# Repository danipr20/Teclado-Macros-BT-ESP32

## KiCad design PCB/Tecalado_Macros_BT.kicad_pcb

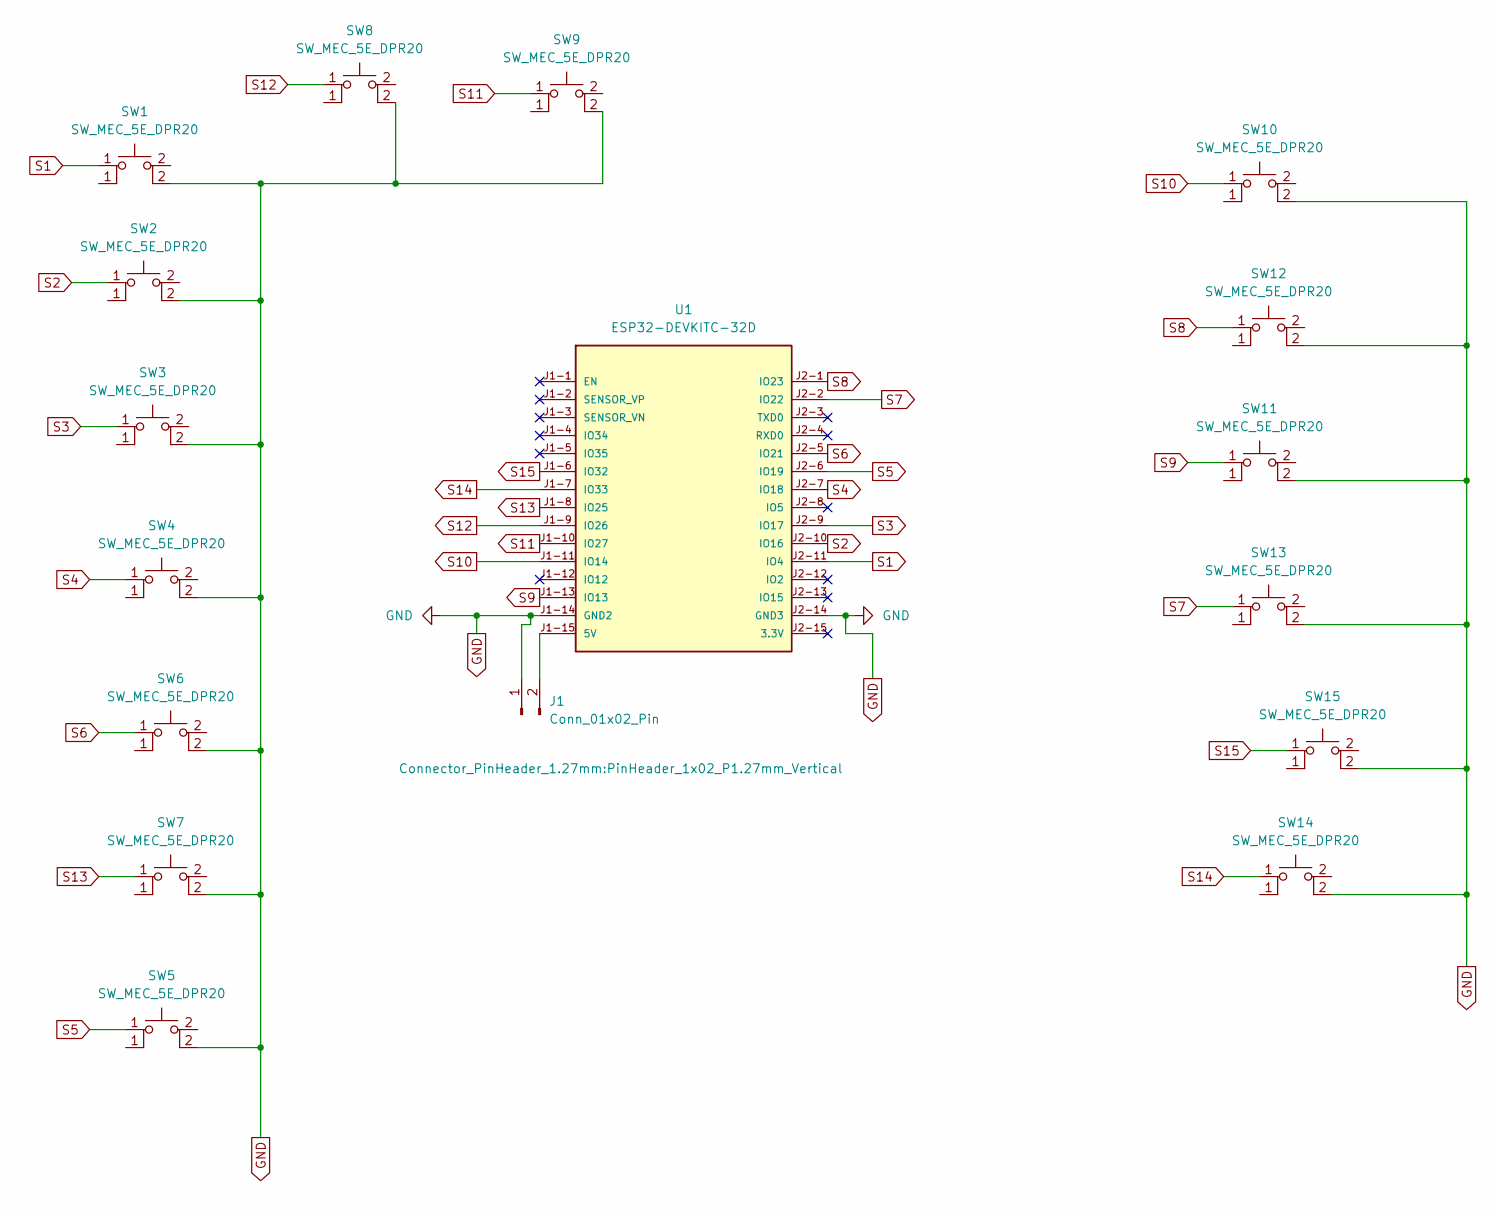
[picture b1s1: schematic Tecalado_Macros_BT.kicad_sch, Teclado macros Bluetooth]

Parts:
J1: Conn_01x02_Pin; PinHeader_1x02_P1.27mm_Vertical
SW1, SW2, SW3, SW4, SW5, SW6, SW7, SW8, SW9, SW10, SW11, SW12, SW13, SW14, SW15: SW_MEC_5E_DPR20; SW_PUSH_6mm_H7.3mm
U1: ESP32-DEVKITC-32D; MODULE_ESP32-DEVKITC-32D; PARTREV V4

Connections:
GND: J1.1, SW1.2, SW2.2, SW3.2, SW4.2, SW5.2, SW6.2, SW7.2, SW8.2, SW9.2, SW10.2, SW11.2, SW12.2, SW13.2, SW14.2, SW15.2, U1.J1-14 (GND2), U1.J2-14 (GND3)
unnamed: J1.2, U1.J1-15 (5V)
S1: SW1.1, U1.J2-11 (IO4)
S2: SW2.1, U1.J2-10 (IO16)
S3: SW3.1, U1.J2-9 (IO17)
S4: SW4.1, U1.J2-7 (IO18)
S5: SW5.1, U1.J2-6 (IO19)
S6: SW6.1, U1.J2-5 (IO21)
S7: SW13.1, U1.J2-2 (IO22)
S8: SW12.1, U1.J2-1 (IO23)
S9: SW11.1, U1.J1-13 (IO13)
S10: SW10.1, U1.J1-11 (IO14)
S11: SW9.1, U1.J1-10 (IO27)
S12: SW8.1, U1.J1-9 (IO26)
S13: SW7.1, U1.J1-8 (IO25)
S14: SW14.1, U1.J1-7 (IO33)
S15: SW15.1, U1.J1-6 (IO32)

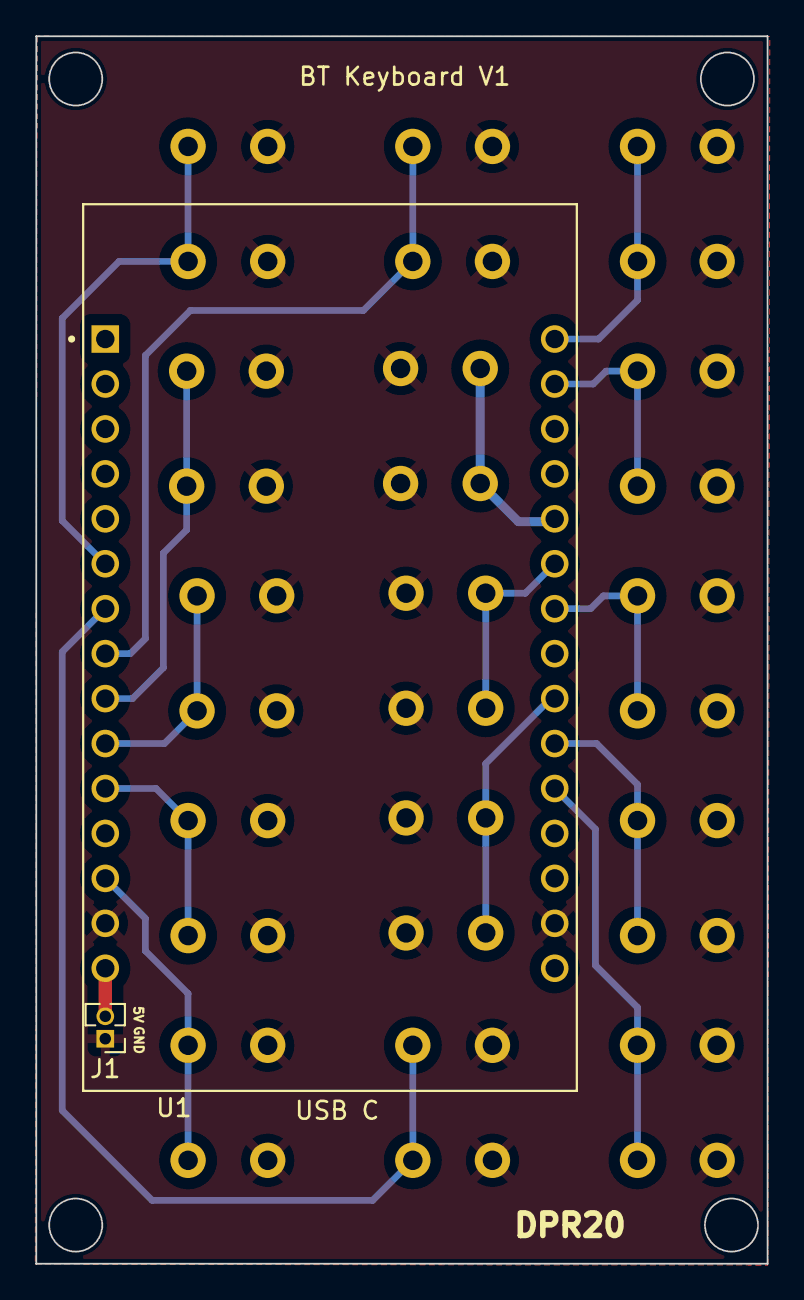
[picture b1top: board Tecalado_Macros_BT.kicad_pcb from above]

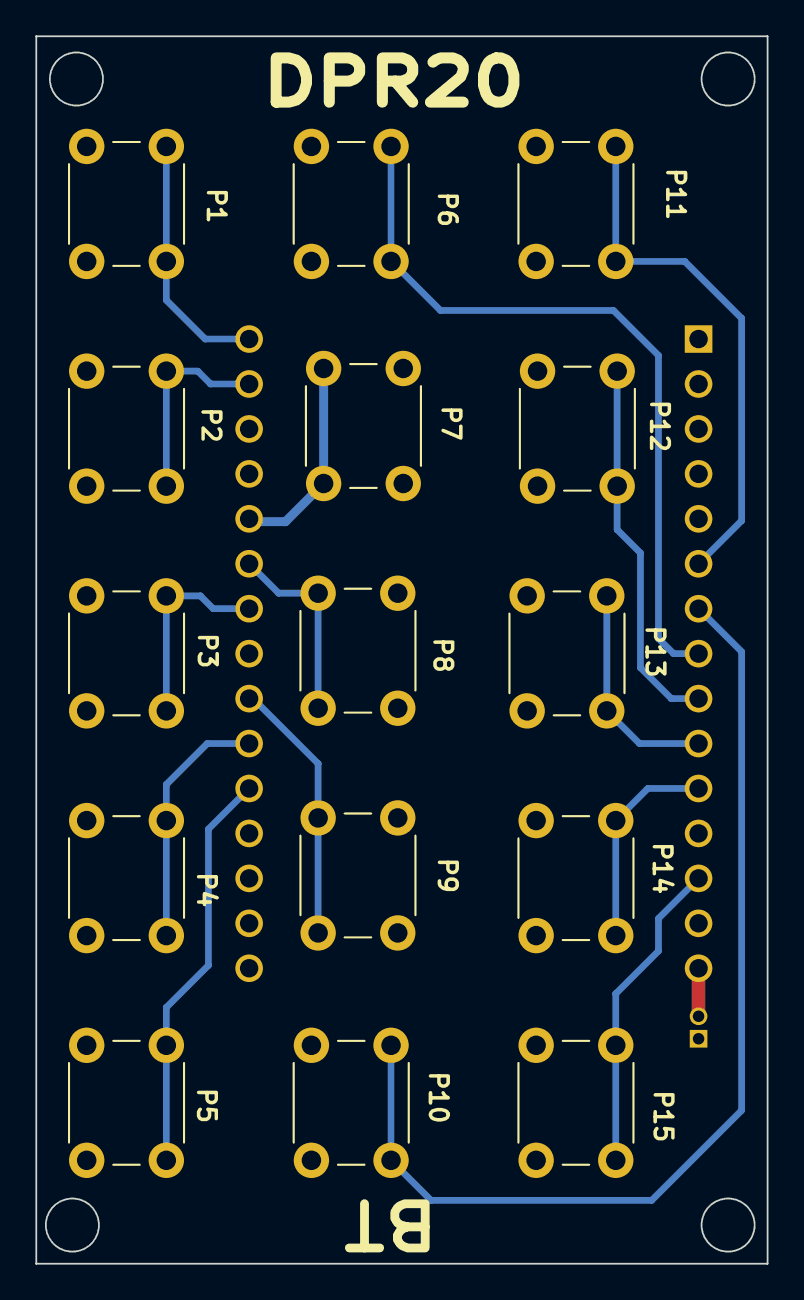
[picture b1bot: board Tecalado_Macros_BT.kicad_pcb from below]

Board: 2 copper layers, 41.3 x 69.4 mm, 17 parts (15 on the bottom side), 17 nets.

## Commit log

2024-09-08 Update Teclado_Macros_BT_Proto.ino
    Actualización de botones:
    Funcionalidad para Automation builder y general
2024-09-08 Unificación de archivos
2024-09-08 añadida la libreria bt keyb
2024-09-12 V1 primera carga basica
2024-09-13 comentarios
2024-09-15 SW EspHome para incluir como dispositivo a Home Assistant y comienzo de version multiperfil
2024-12-02 Actualizacion mapeado teclado V1 (Basic)
2024-12-02 Reajuste de mapeado, V1 (Basic)
2024-12-09 Adicion de envio de contrasenas
2024-12-24 Creacion de nuevo funcionamiento BT Serial
